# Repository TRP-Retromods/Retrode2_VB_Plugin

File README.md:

# Retrode2 Virtual Boy Plugin
Virtual Boy plugin for the Retrode 2. Support RAM/ROM acces. Should be working with Hyper Fighting

Based on JonY and Skaman works. I've added a 74HC4053D and a switch to make it work with Hyper Fighting. It's working with classic VB Games (Rom/Save game) but unfortunately I can't test it with Hyper Fighting (because game was a limited run and is freaking expensive.

You'll find in the depository:
- The PCB (Eagle File and Gerber Files in a .ZIP) - Yes you need to print the small part on the top.
- The STL file of the cart sled. I recommand ABS or PETG for printing material.
- The PSD file for the label. Work well with decal paper

You'll need to assemble it:
- a 74HC4053D in SOIC package
- a SPDT switch https://www.digikey.ca/product-detail/en/c-k/OS102011MS2QN1/CKN9565-ND/411602
- a right angle 1.7mm spacing row male header. You have 2x60pins to populate. I used two https://www.digikey.ca/product-detail/en/M50-3905042/952-1704-ND/2762133 to make one cart slot.
- an empty genesis cart shell.

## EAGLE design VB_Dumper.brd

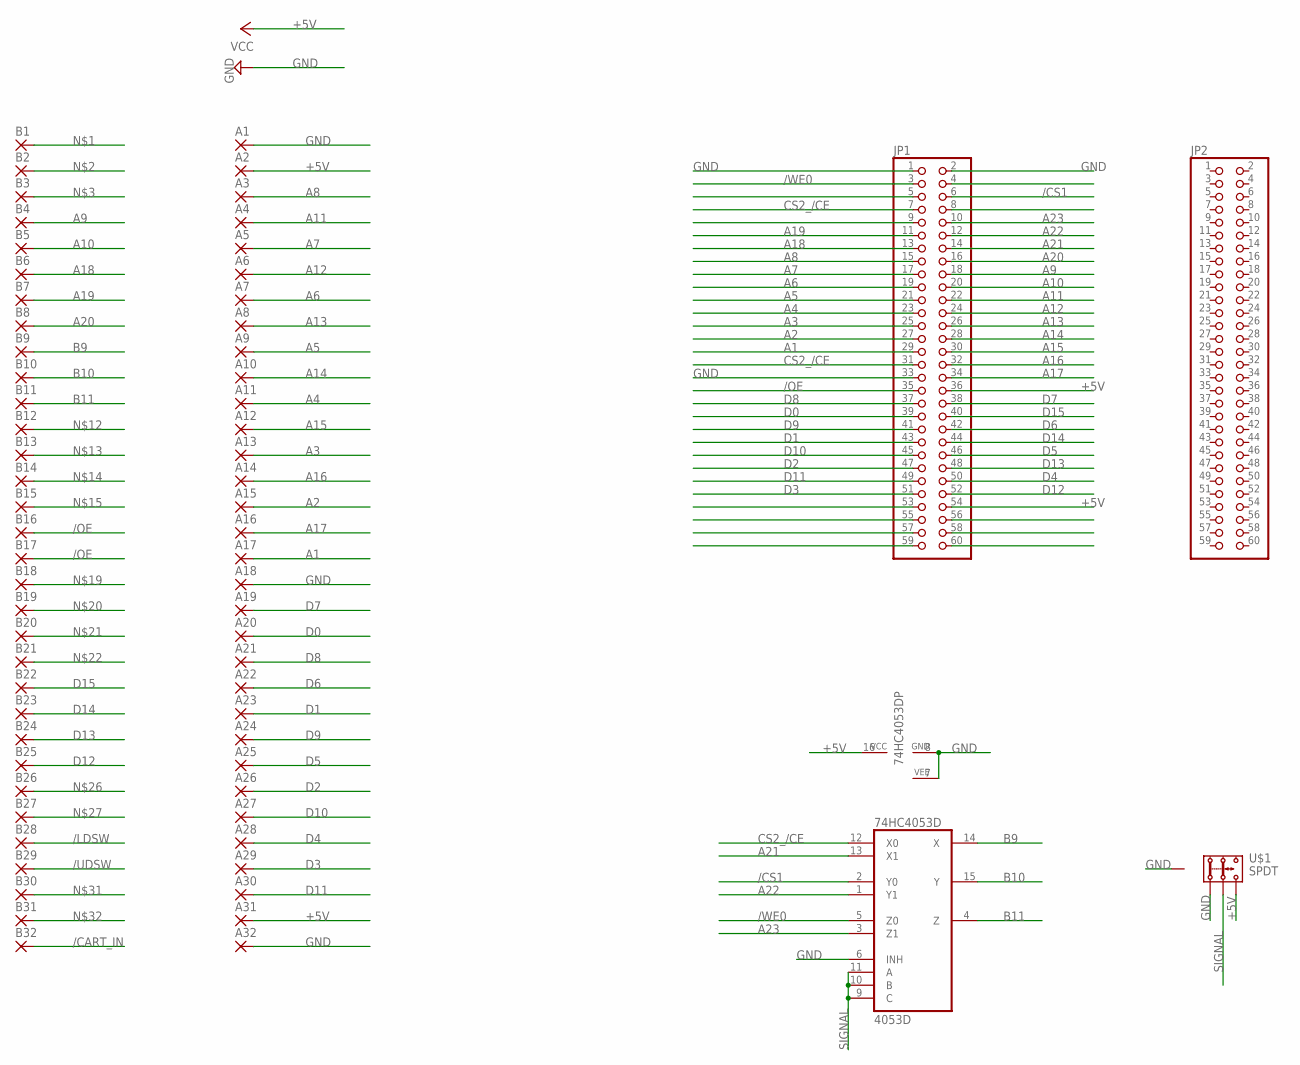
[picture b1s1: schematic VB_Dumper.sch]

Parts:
74HC4053D: 4053D; SO16
A1, A2, A3, A4, A5, A6, A7, A8, A9, A10, A11, A12, A13, A14, A15, A16, A17, A18, A19, A20, A21, A22, A23, A24, A25, A26, A27, A28, A29, A30, A31, A32: SMD2; SMD1,27-2,54
B1, B2, B3, B4, B5, B6, B7, B8, B9, B10, B11, B12, B13, B14, B15, B16, B17, B18, B19, B20, B21, B22, B23, B24, B25, B26, B27, B28, B29, B30, B31, B32: SMD2; SMD1,27-2,54
JP1, JP2: PINHD-2X30_2.00; 2X30M
U$1: SPDT

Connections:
+5V: 74HC4053D.16 (VCC), A2.1, A31.1, JP1.36, JP1.54, U$1.3.2
/CART_IN: B32.1
/CS1: 74HC4053D.2 (Y0), JP1.6
/LDSW: B28.1
/OE: B16.1, B17.1, JP1.35
/UDSW: B29.1
/WE0: 74HC4053D.5 (Z0), JP1.3
A1: A17.1, JP1.29
A2: A15.1, JP1.27
A3: A13.1, JP1.25
A4: A11.1, JP1.23
A5: A9.1, JP1.21
A6: A7.1, JP1.19
A7: A5.1, JP1.17
A8: A3.1, JP1.15
A9: B4.1, JP1.18
A10: B5.1, JP1.20
A11: A4.1, JP1.22
A12: A6.1, JP1.24
A13: A8.1, JP1.26
A14: A10.1, JP1.28
A15: A12.1, JP1.30
A16: A14.1, JP1.32
A17: A16.1, JP1.34
A18: B6.1, JP1.13
A19: B7.1, JP1.11
A20: B8.1, JP1.16
A21: 74HC4053D.13 (X1), JP1.14
A22: 74HC4053D.1 (Y1), JP1.12
A23: 74HC4053D.3 (Z1), JP1.10
B9: 74HC4053D.14 (X), B9.1
B10: 74HC4053D.15 (Y), B10.1
B11: 74HC4053D.4 (Z), B11.1
CS2_/CE: 74HC4053D.12 (X0), JP1.7, JP1.31
D0: A20.1, JP1.39
D1: A23.1, JP1.43
D2: A26.1, JP1.47
D3: A29.1, JP1.51
D4: A28.1, JP1.50
D5: A25.1, JP1.46
D6: A22.1, JP1.42
D7: A19.1, JP1.38
D8: A21.1, JP1.37
D9: A24.1, JP1.41
D10: A27.1, JP1.45
D11: A30.1, JP1.49
D12: B25.1, JP1.52
D13: B24.1, JP1.48
D14: B23.1, JP1.44
D15: B22.1, JP1.40
GND: 74HC4053D.6 (INH), 74HC4053D.7 (VEE), 74HC4053D.8 (GND), A1.1, A18.1, A32.1, JP1.1, JP1.2, JP1.33, U$1.1.2, U$1.P$1 (GND), U$1.P$2 (GND)
SIGNAL: 74HC4053D.9 (C), 74HC4053D.10 (B), 74HC4053D.11 (A), U$1.2.2

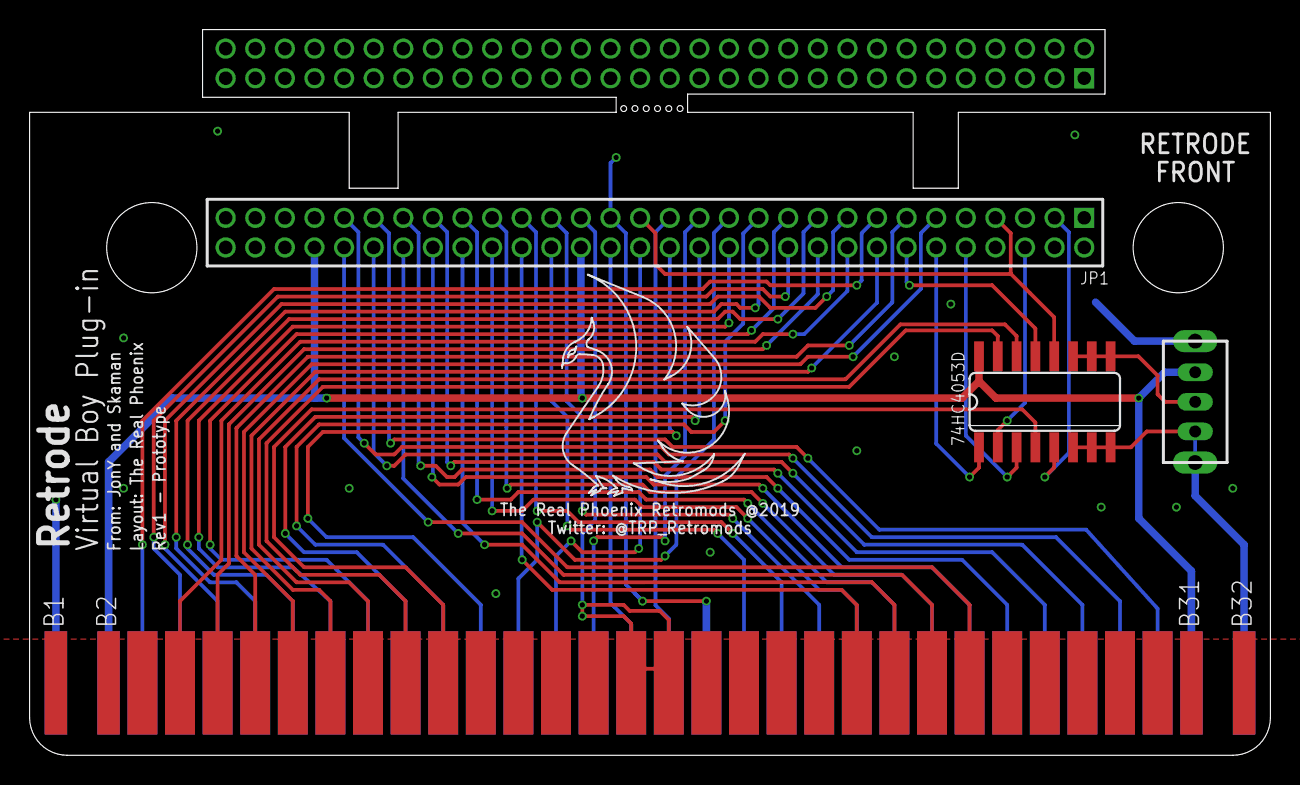
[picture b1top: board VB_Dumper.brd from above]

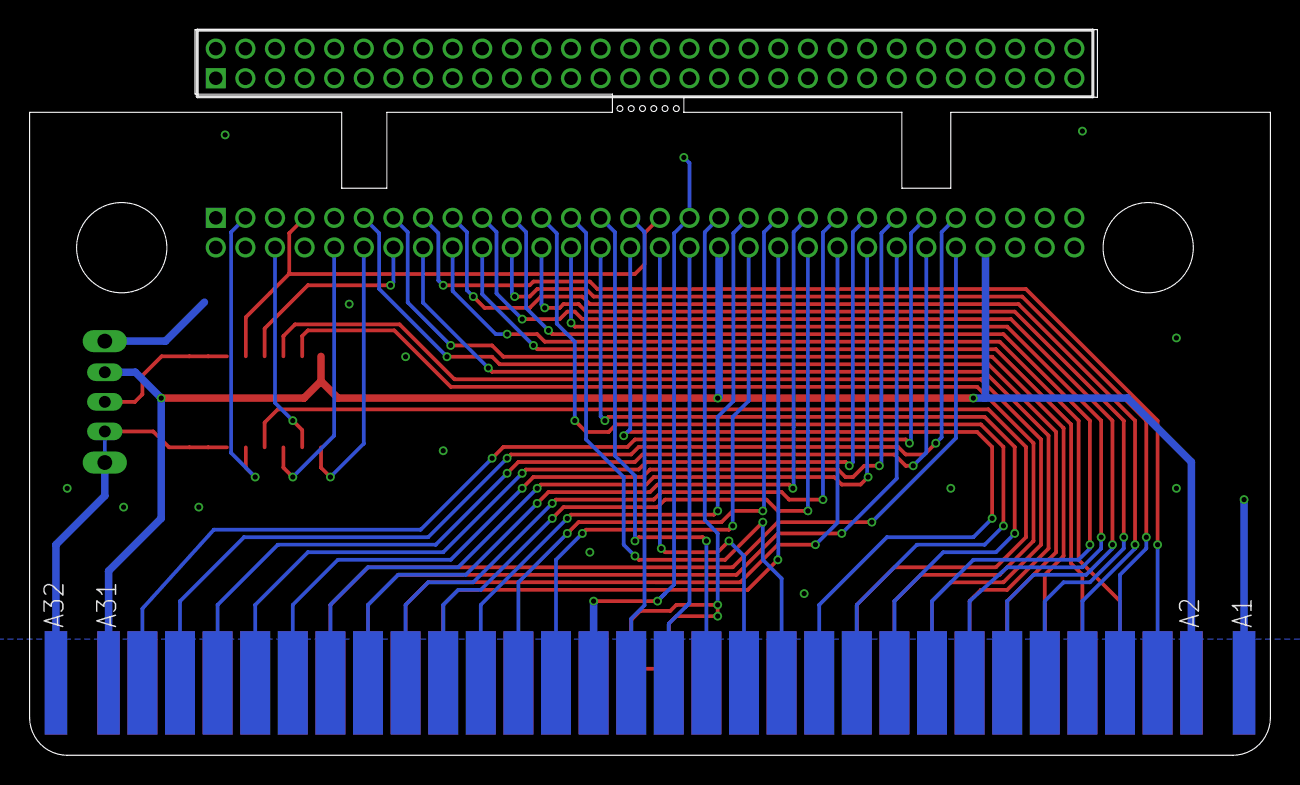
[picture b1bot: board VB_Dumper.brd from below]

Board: 2 copper layers, 83.8 x 49.0 mm, 69 parts (33 on the bottom side), 49 nets.

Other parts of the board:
U$2: LOGO
